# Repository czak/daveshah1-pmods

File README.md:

This is just a fork of https://github.com/daveshah1/pmods. All credit to @daveshah1.
I'm making some changes to the LCD PMOD schematic/layout so I can build it with parts that I have or can easily find:

* different FFC connector
* FAN5333B instead of TPS61165
* different inductor footprint
* probably some more

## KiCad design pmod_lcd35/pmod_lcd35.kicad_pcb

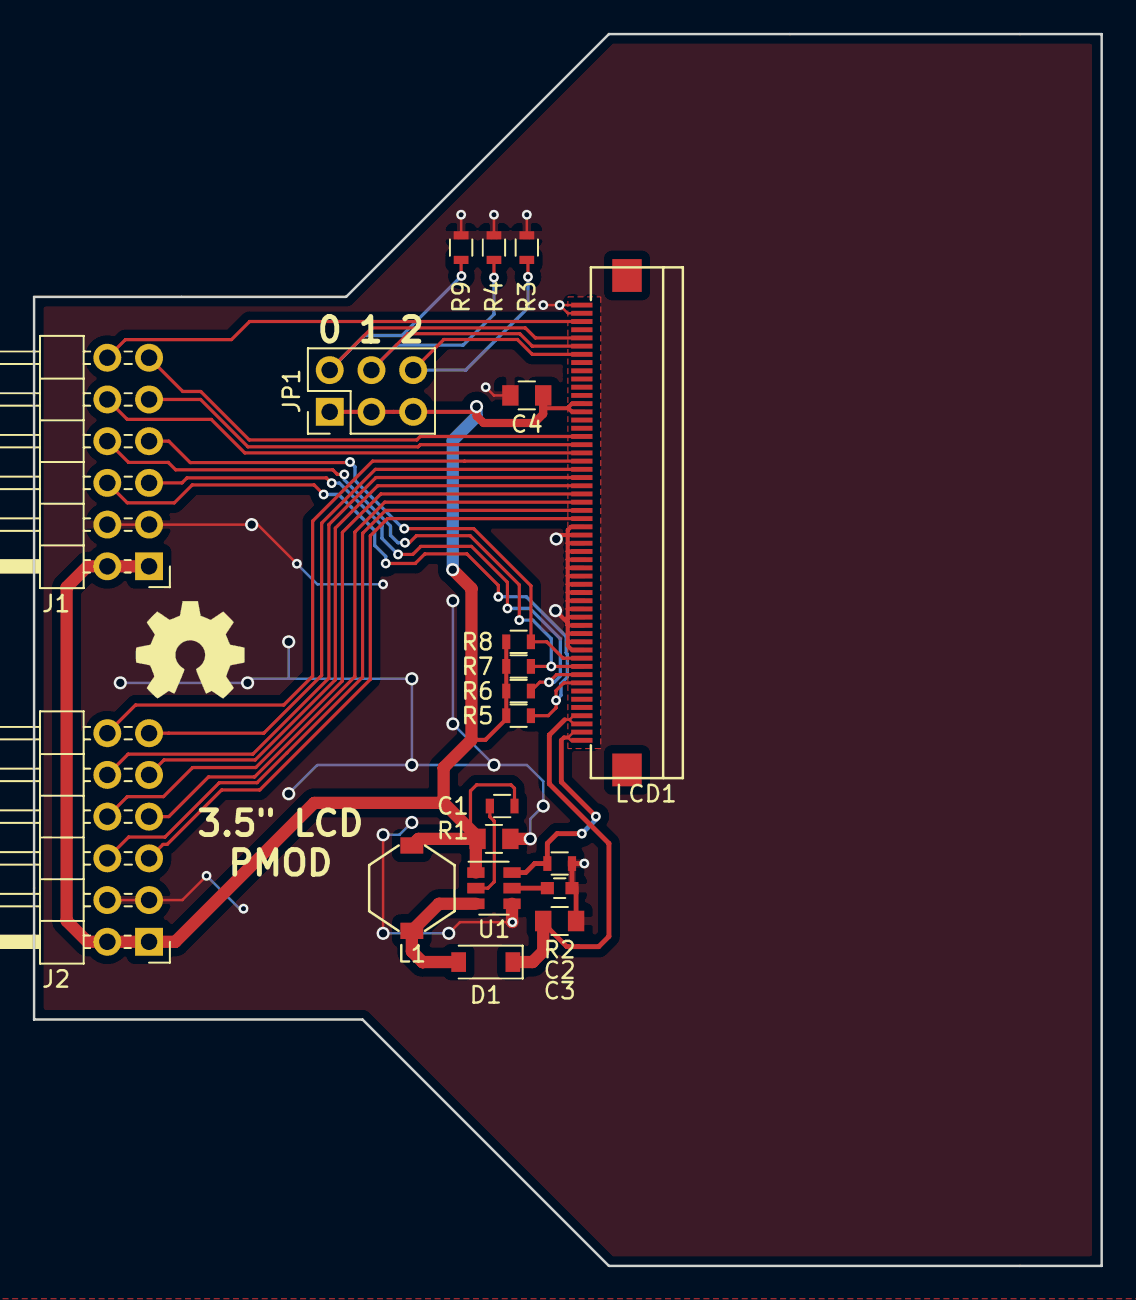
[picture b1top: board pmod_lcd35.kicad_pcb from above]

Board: 2 copper layers, 65.0 x 75.0 mm, 20 parts (0 on the bottom side), 26 nets.

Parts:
C1, C4: 10µ; C_0805
C2: 220n; C_0603
C3: 1µ/50V; C_0805
D1: MBR0540; D_SOD-123
J1: PMOD_0; PMOD_2x06_2.54mm
J2: PMOD_1; PMOD_2x06_2.54mm
JP1: JMPx3; Pin_Header_Straight_2x03_Pitch2.54mm
L1: 10µH/A915AY-100M; muRata_L_2020
LCD1: LQ035NC111; CviLux_CF25541D0R0-05-NH
R1, R3, R4, R5, R6, R7, R8, R9: 10k; R_0603
R2: 10; R_0603
U1: TPS61165; SOT-23-6

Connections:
+3V3: C1.1, C4.1, J1.6, J1.12, J2.6, J2.12, JP1.1, JP1.3, JP1.5, L1.1, LCD1.41, LCD1.42, R1.2, R5.2, R6.2, R7.2, R8.2, U1.1
/DCLK: J1.1, LCD1.38
/DEN: J1.7, LCD1.52
/DX0: J2.4, LCD1.28
/DX1: J2.10, LCD1.29
/DX2: J2.3, LCD1.30
/DX3: J2.9, LCD1.31
/DX4: J2.2, LCD1.32
/DX5: J2.8, LCD1.33
/DX6: J2.1, LCD1.34
/DX7: J2.7, LCD1.35
/HSYNC: J1.8, LCD1.36
/IF0: JP1.2, LCD1.50, R9.1
/IF1: JP1.4, LCD1.49, R4.1
/IF2: JP1.6, LCD1.48, R3.1
/SPCLK: J1.9, LCD1.10, R7.1
/SPDAT: J1.3, LCD1.11, R8.1
/SPENA: J1.4, LCD1.9, R6.1
/VBL+: C3.1, D1.1, LCD1.3, LCD1.4
/VBL-: LCD1.1, LCD1.2, R2.1, U1.6
/VSYNC: J1.2, LCD1.37
/~RESET: J1.10, LCD1.8, R5.1
GND: C1.2, C2.2, C3.2, C4.2, J1.5, J1.11, J2.5, J2.11, LCD1.12, LCD1.13, LCD1.14, LCD1.15, LCD1.16, LCD1.17, LCD1.18, LCD1.19, LCD1.20, LCD1.21, LCD1.22, LCD1.23, LCD1.24, LCD1.25, LCD1.26, LCD1.27, LCD1.53, LCD1.54, R2.2, R3.2, R4.2, R9.2, U1.4
unnamed: C2.1, U1.5
unnamed: D1.2, L1.2, U1.3
unnamed: R1.1, U1.2

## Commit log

2020-05-29 Add sym-lib-table
2020-05-29 Add full gitignore
2020-05-29 Import schematic to 5.1.6
2020-05-29 Add CviLux FFC connector footprint
2020-05-29 Move anchor
2020-05-29 Change FFC footprint
